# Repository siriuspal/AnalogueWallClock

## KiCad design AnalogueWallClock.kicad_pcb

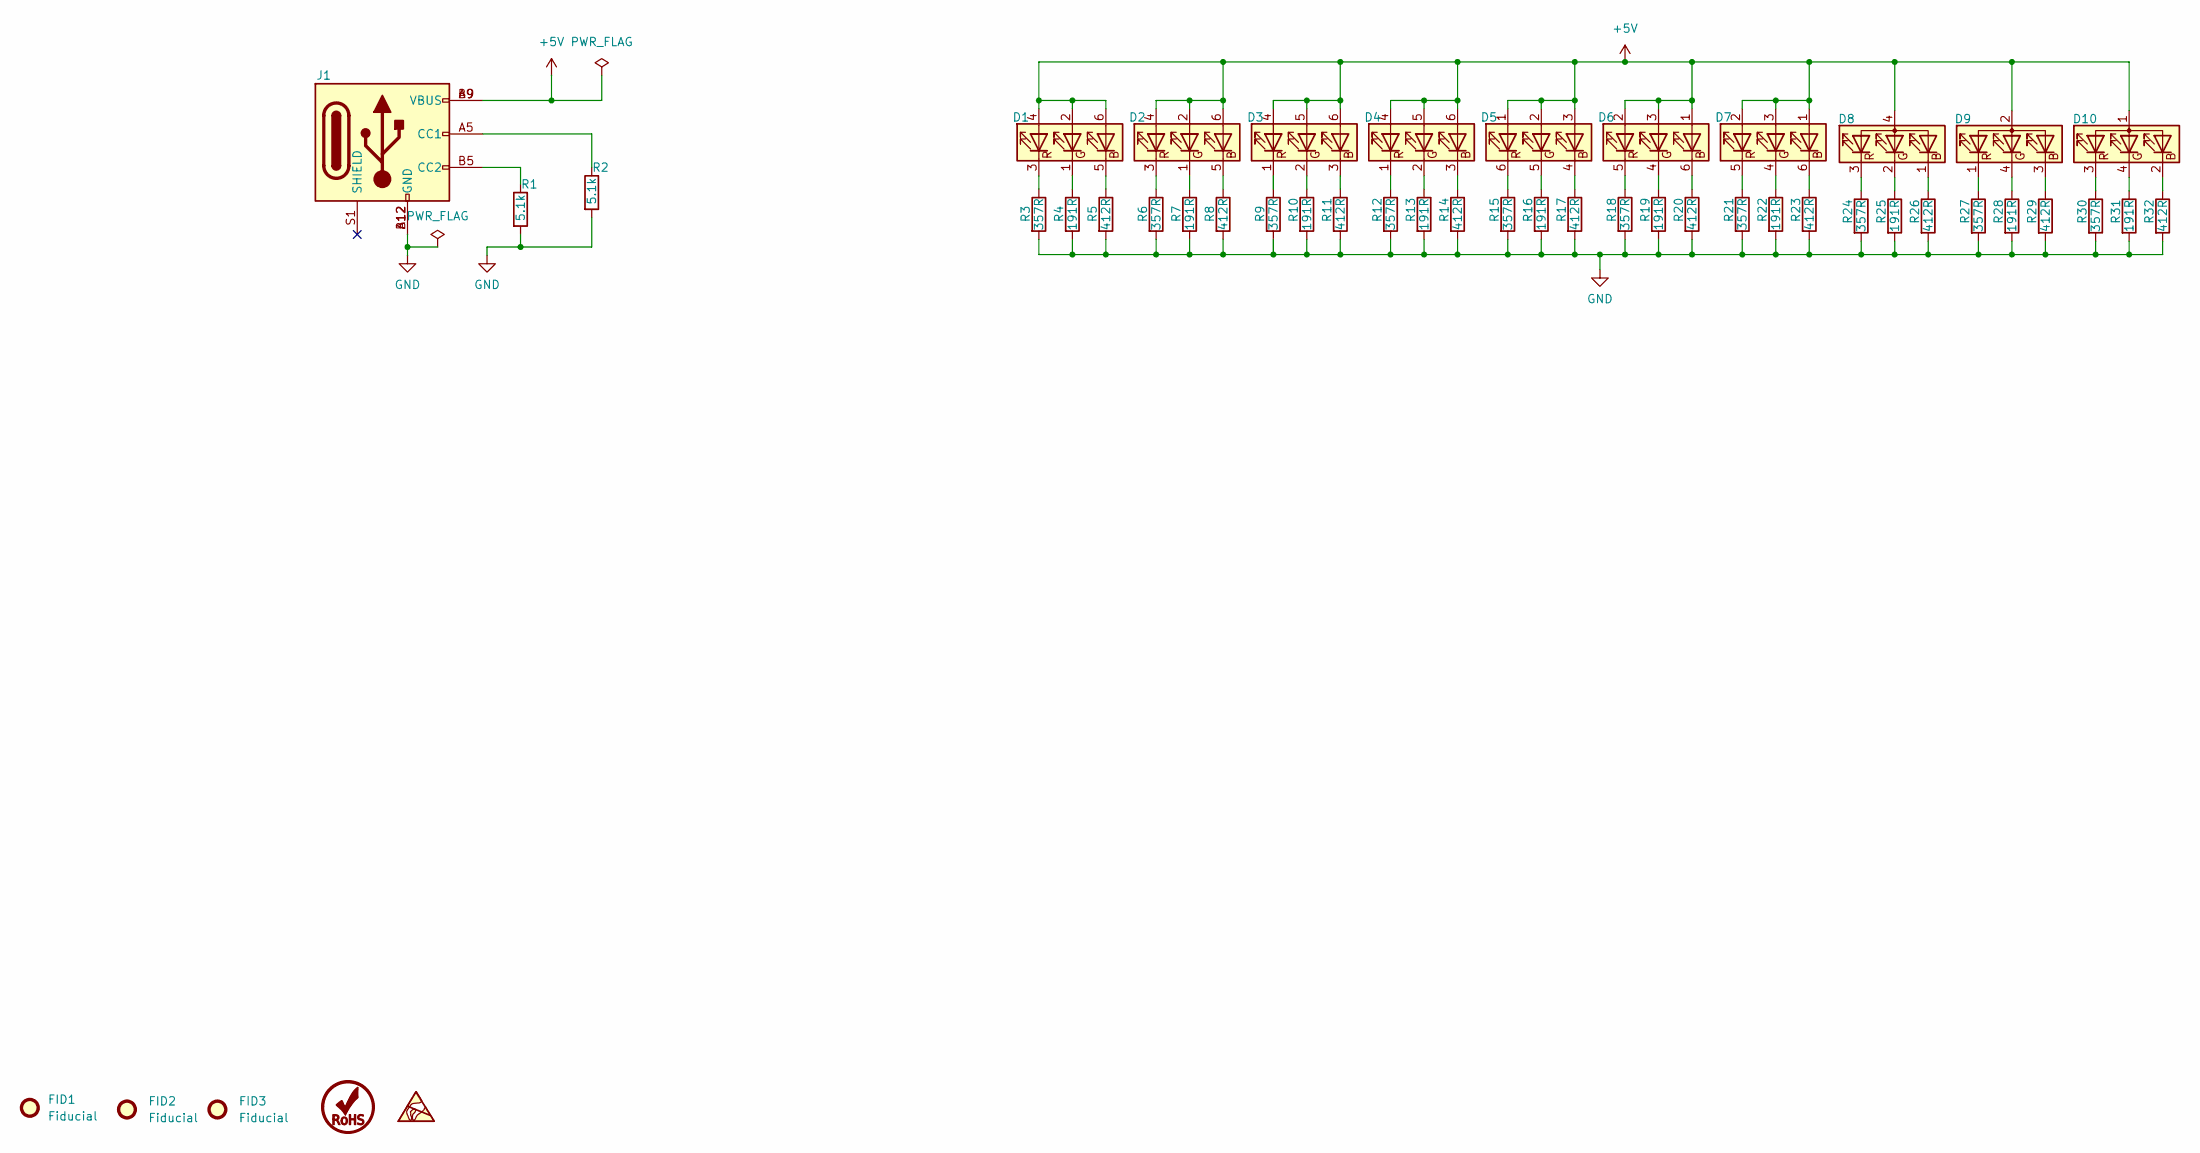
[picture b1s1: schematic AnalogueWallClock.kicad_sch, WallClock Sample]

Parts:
D1: LED_RGB_1; 19-337C_RSBHGHC-A88_4T_Cutout; MPN 19-337C/RSBHGHC-A88/4T; Digi-Key Part Number 1080-1631-1-ND
D2: LED_RGB_1; 19-337C_RSBHGHC-A88_4T_Hole; MPN 19-337C/RSBHGHC-A88/4T; Digi-Key Part Number 1080-1631-1-ND
D3: LED_RGB_2; APF3236SEEZGQBDC_Cutout; MPN APF3236SEEZGQBDC; Digi-Key Part Number 754-2155-1-ND
D4: LED_RGB_2; APF3236SEEZGQBDC_Hole; MPN APF3236SEEZGQBDC; Digi-Key Part Number 754-2155-1-ND
D5: LED_RGB_4; CLP6C-FKB-CK1P1G1BB7R3R3_Hole; MPN CLP6C-FKB-CK1P1G1BB7R3R3; Digi-Key Part Number CLP6C-FKB-CK1P1G1BB7R3R3CT-ND
D6: LED_RGB_5; SMLVN6RGB1W1‎_Cutout; MPN SMLVN6RGB1W1; Digi-Key Part Number 846-1187-1-ND
D7: LED_RGB_5; SMLVN6RGB1W1‎_Hole; MPN SMLVN6RGB1W1; Digi-Key Part Number 846-1187-1-ND
D8: LED_BGRA_1; QBLP677R-RGB; MPN QBLP677R-RGB; Digi-Key Part Number 1516-1282-1-ND
D9: LED_RABG; XZMDKCBDDG45S-9; MPN XZMDKCBDDG45S-9; Digi-Key Part Number 1497-1257-1-ND
D10: LED_ABRG; 156120M173000; MPN 156120M173000; Digi-Key Part Number 732-13408-1-ND
FID1, FID2, FID3: Fiducial; Fiducial_0.75mm_Mask1.5mm
J1: USB_C; USB-C-PowerOnly; MPN KUSBX-SMT-CS-6-BTR; Digi-Key Part Number 2092-KUSBX-SMT-CS-6-BCT-ND
R1, R2: 5.1k; R_0603_1608Metric_Pad0.98x0.95mm_HandSolder; MPN RMCF0603FT5K10; Digi-Key Part Number RMCF0603FT5K10CT-ND
R3, R6, R9, R12, R15, R18, R21, R24, R27, R30: 357R; R_0603_1608Metric_Pad0.98x0.95mm_HandSolder; MPN RMCF0603FT357R; Digi-Key Part Number 738-RMCF0603FT357RCT-ND
R4, R7, R10, R13, R16, R19, R22, R25, R28, R31: 191R; R_0603_1608Metric_Pad0.98x0.95mm_HandSolder; MPN RMCF0603FT191R; Digi-Key Part Number 738-RMCF0603FT191RCT-ND
R5, R8, R11, R14, R17, R20, R23, R26, R29, R32: 412R; R_0603_1608Metric_Pad0.98x0.95mm_HandSolder; MPN RMCF0603FT412R; Digi-Key Part Number RMCF0603FT412RCT-ND

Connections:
+5V: D1.2 (GA), D1.4 (RA), D1.6 (BA), D2.2 (GA), D2.4 (RA), D2.6 (BA), D3.4 (RA), D3.5 (GA), D3.6 (BA), D4.4 (RA), D4.5 (GA), D4.6 (BA), D5.1 (RA), D5.2 (GA), D5.3 (BA), D6.1 (BA), D6.2 (RA), D6.3 (GA), D7.1 (BA), D7.2 (RA), D7.3 (GA), D8.4 (A), D9.2 (A), D10.1 (A), J1.A9 (VBUS), J1.B9 (VBUS)
GND: J1.A12 (GND), J1.B12 (GND), R1.2, R2.2, R3.2, R4.2, R5.2, R6.2, R7.2, R8.2, R9.2, R10.2, R11.2, R12.2, R13.2, R14.2, R15.2, R16.2, R17.2, R18.2, R19.2, R20.2, R21.2, R22.2, R23.2, R24.2, R25.2, R26.2, R27.2, R28.2, R29.2, R30.2, R31.2, R32.2
unnamed: D1.1 (GK), R4.1
unnamed: D1.3 (RK), R3.1
unnamed: D1.5 (BK), R5.1
unnamed: D2.1 (GK), R7.1
unnamed: D2.3 (RK), R6.1
unnamed: D2.5 (BK), R8.1
unnamed: D3.1 (RK), R9.1
unnamed: D3.2 (GK), R10.1
unnamed: D3.3 (BK), R11.1
unnamed: D4.1 (RK), R12.1
unnamed: D4.2 (GK), R13.1
unnamed: D4.3 (BK), R14.1
unnamed: D5.4 (BK), R17.1
unnamed: D5.5 (GK), R16.1
unnamed: D5.6 (RK), R15.1
unnamed: D6.4 (GK), R19.1
unnamed: D6.5 (RK), R18.1
unnamed: D6.6 (BK), R20.1
unnamed: D7.4 (GK), R22.1
unnamed: D7.5 (RK), R21.1
unnamed: D7.6 (BK), R23.1
unnamed: D8.1 (BK), R26.1
unnamed: D8.2 (GK), R25.1
unnamed: D8.3 (RK), R24.1
unnamed: D9.1 (RK), R27.1
unnamed: D9.3 (BK), R29.1
unnamed: D9.4 (GK), R28.1
unnamed: D10.2 (BK), R32.1
unnamed: D10.3 (RK), R30.1
unnamed: D10.4 (GK), R31.1
unnamed: J1.A5 (CC1), R2.1
unnamed: J1.B5 (CC2), R1.1

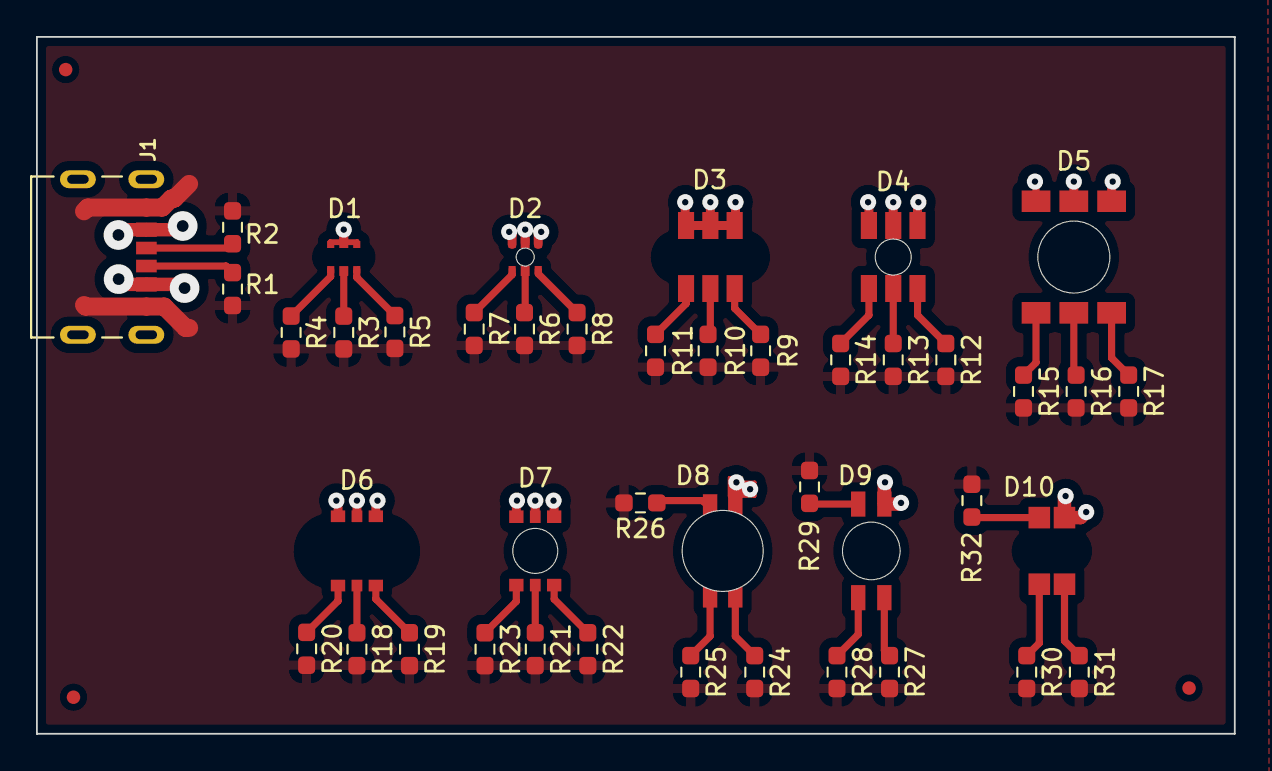
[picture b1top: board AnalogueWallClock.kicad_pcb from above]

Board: 2 copper layers, 66.5 x 38.7 mm, 46 parts (0 on the bottom side), 34 nets.

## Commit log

2022-01-01 added ignore
2022-01-02 completed schematics
2022-01-04 test pcb complete
2022-01-04 removed datasheet folder sync
2022-01-04 calc updated
2022-01-04 added backup to ignore
2022-01-04 added backup to gitignore
